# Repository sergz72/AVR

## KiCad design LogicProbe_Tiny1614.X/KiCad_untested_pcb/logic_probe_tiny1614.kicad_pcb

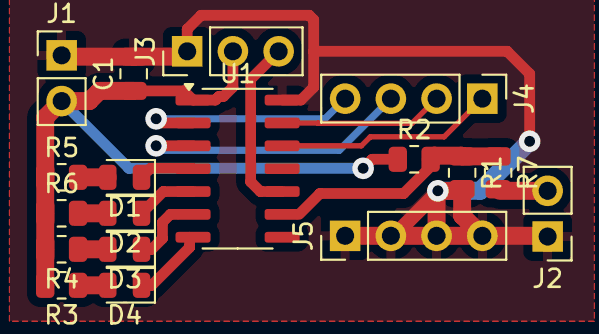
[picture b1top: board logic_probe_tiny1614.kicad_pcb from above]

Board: 2 copper layers, 18 parts (0 on the bottom side), 17 nets.

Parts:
C1: 100n; C_0805_2012Metric
D1, D2, D3, D4: LED; LED_0805_2012Metric
J1: VCC; PinHeader_1x02_P2.54mm_Vertical
J2: IN; PinHeader_1x02_P2.54mm_Vertical
J3: DEBUG; PinHeader_1x03_P2.54mm_Vertical
J4, J5: SW; PinHeader_1x04_P2.54mm_Vertical
R1: 20k; R_0805_2012Metric
R2: 68k; R_0805_2012Metric
R3, R4, R5, R6: 1k; R_0805_2012Metric
R7: 300; R_0805_2012Metric
U1: ATtiny1614-SS; SOIC-14_3.9x8.7mm_P1.27mm

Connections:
GND: C1.2, J1.1, J2.1, J3.1, J5.1, J5.2, J5.3, J5.4, R1.2, U1.14 (GND)
unnamed: D1.2 (A), R5.2
unnamed: D1.1 (K), U1.4 (PA6)
unnamed: D2.2 (A), R6.2
unnamed: D2.1 (K), U1.5 (PA7)
unnamed: D3.2 (A), R4.1
unnamed: D3.1 (K), U1.6 (PB3)
unnamed: D4.2 (A), R3.1
unnamed: D4.1 (K), U1.7 (PB2)
unnamed: C1.1, J1.2, J3.2, R2.1, R3.2, R4.2, R5.1, R6.1, U1.1 (VCC)
unnamed: J2.2, R7.2
unnamed: J3.3, U1.10 (~RESET/PA0)
unnamed: J4.1, U1.12 (PA2)
unnamed: J4.2, U1.13 (PA3)
unnamed: J4.3, U1.3 (PA5)
unnamed: J4.4, U1.2 (PA4)
unnamed: R1.1, R2.2, R7.1, U1.9 (PB0)

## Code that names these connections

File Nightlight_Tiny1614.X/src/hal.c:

#include "board.h"
#include <avr/io.h>
#include <avr/sleep.h>
#include <avr/interrupt.h>
#include <avr/cpufunc.h>
#include <avr/wdt.h>
#include "usart_handler.h"
#include <stdio.h>
#include <rtc_pcf8563.h>
#include <i2c_tiny1614.h>

FUSES = {
  .WDTCFG = 0x07, // WDTCFG {PERIOD=0.5s, WINDOW=OFF}
  .BODCFG = 0x55, // BODCFG {SLEEP=ENABLED, ACTIVE=ENABLED, SAMPFREQ=125HZ, LVL=BODLEVEL2} 2.6v
  .OSCCFG = 0x01, // OSCCFG {FREQSEL=16MHZ, OSCLOCK=CLEAR}
  .TCD0CFG = 0x00, // TCD0CFG {CMPA=CLEAR, CMPB=CLEAR, CMPC=CLEAR, CMPD=CLEAR, CMPAEN=CLEAR, CMPBEN=CLEAR, CMPCEN=CLEAR, CMPDEN=CLEAR}
  .SYSCFG0 = 0xF6, // SYSCFG0 {EESAVE=CLEAR, RSTPINCFG=UPDI, CRCSRC=NOCRC}
  .SYSCFG1 = 0x07, // SYSCFG1 {SUT=64MS}
  .APPEND = 0x00, // APPEND {APPEND=User range:  0x0 - 0xFF}
  .BOOTEND = 0x00, // BOOTEND {BOOTEND=User range:  0x0 - 0xFF}
};

LOCKBITS = 0xC5; // {LB=NOLOCK}

volatile unsigned char timer_interrupt, rtc_interrupt;

#ifdef USART_ENABLED
int usart_fputchar(char c, FILE *stream);
FILE usart_stdout = FDEV_SETUP_STREAM(usart_fputchar, NULL, _FDEV_SETUP_WRITE);
#endif

// RTC counter interrupt
ISR (RTC_PIT_vect)
{
  wdt_reset();
  timer_interrupt = 1;
  RTC.PITINTFLAGS = 1; // clear interrupt flag
}

ISR (INT_PORT_vect)
{
  if (INT_PORT.INTFLAGS & (1 << INT_PIN))
    rtc_interrupt = 1;
  INT_PORT.INTFLAGS = 0xFF;
}

#ifdef USART_ENABLED
ISR (USART0_RXC_vect)
{
  if (USART0.STATUS & 0x80)
  {
    unsigned char c = USART0.RXDATAL;
    usart_interrupt_handler(c);
  }
}
#endif

/*
 * PB0(9)  SCL
 * PB1(8)  SDA
 * PB2(7)  TX
 * PB3(6)  RX
 * PA0(10) UPDI
 * PA1(11) INT
 * PA2(12) LED_TIMER
 * PA3(13) LED_BATTERY
 * PA4(2)  TCD WOA
 * PA5(3)
 * PA6(4)  AC1 AINP1
 * PA7(5)
 */

static void
InitPorts (void)
{
  LED_TIMER_PORT.DIRSET = 1 << LED_TIMER_PIN;
  LED_BATTERY_PORT.DIRSET = 1 << LED_BATTERY_PIN;
  INT_PORT.INT_PINCTRL = 0b00001011; // pullup enable, falling edge interrupt
}

static void
InitRTC (void)
{
  RTC.PITCTRLA   = 0b01011001; // enabled, interrupt each 4096 cycles
  RTC.PITINTCTRL = 1; // periodic interrupt is enabled
}

static void InitVREF(void)
{
  VREF.CTRLA = 0b01000000; // ADC0 reference = 1.5v, DAC0 reference = 0.55v
  VREF.CTRLC = 0b00000000; // ADC1 reference = 0.55v, DAC1 reference = 0.55v
  VREF.CTRLB = 0b00001010; // Enable references for ADC0, DAC1
}

static void InitDAC1(void)
{
  DAC1.DATA  = DAC1_VALUE;
  DAC1.CTRLA = 0x01; // DAC enable
}

static void InitComparator1(void)
{
  PORTA.PIN6CTRL = 4; // digital intput buffer disable
  
  AC1.MUXCTRLA = 0b00001011; // invert output, positive input - AINP1, negative input - DAC
  AC1.CTRLA    = 0b00000001; // Comparator enable, output disable

  // 2. Route AC0 output to Event System Channel 0
  EVSYS.ASYNCCH0   = EVSYS_ASYNCCH0_AC1_OUT_gc; // AC1_OUT
  EVSYS.ASYNCUSER6 = 3; // ASYNCCH0 -> Timer Counter D 0 Event 0
}

static void
InitADC0(void)
{
  ADC0.MUXPOS   = 0x1D; // internal reference
  ADC0.CTRLB    = 0b00000000; // No accumulation
  ADC0.CTRLC    = 0b01010011; // Prescaler: 16, REFSEL = VDD, Reduced size of sampling capacitance. Recommended for higher reference voltages.
  ADC0.SAMPCTRL = 0; // sampling time - two adc cycles
  ADC0.CTRLA    = 0b00000001; // ADC enabled
}

static void
InitPWM(void)
{
  TCD0.CTRLB   = 0; // WGMODE = OneRamp
  TCD0.CTRLC   = 0;
  TCD0.CTRLD   = 0;
  TCD0.CTRLE   = 0;
  TCD0.CMPASET = 0;
  TCD0.CMPACLR = PWM_DUTY;
  TCD0.CMPBSET = 0;
  TCD0.CMPBCLR = PWM_CMP_CALC(PWM_FREQUENCY); // period
  TCD0.INPUTCTRLA = 6; // WAIT
  TCD0.EVCTRLA = 0b10010101; // Async event, rising edge, fault event, enabled
  
  PWM_PORT.DIRSET = 1 << PWM_PIN;
}

#ifdef USART_ENABLED
static void
InitUsart (void)
{
  stdout = &usart_stdout;
  
  // read signed error
  signed char sigrow_val = SIGROW.OSC16ERR3V;
  // ideal BAUD register value
  signed long baud_reg_val = CLK_PER * 4L / USART_BAUD; 
  baud_reg_val *= 1024 + sigrow_val; // sum resolution + error
  baud_reg_val /= 1024; // divide by resolution  
  
  USART0.BAUD  = (unsigned short)baud_reg_val;
  USART0.CTRLA = 0b10000000; // Receive complete interrupt enable
  USART0.CTRLB = 0b11000000; // Receiver and transmitter enabled
  // CMODE Asynchronous Mode; UCPHA enabled; UDORD disabled; CHSIZE Character size: 8 bit; PMODE No Parity; SBMODE 1 stop bit; 
  USART0.CTRLC = 0x3;
  USART0.DBGCTRL = 1;
  
  USART_PORT.OUTSET = 1 << USART_TX_PIN;
  USART_PORT.DIRSET = 1 << USART_TX_PIN;
  USART_PORT.USART_RXPINCTRL = 8; // pullup enable
}

void usart_putchar(char c)
{
  while (!(USART0.STATUS & USART_DREIF_bm))
    ;
  USART0.TXDATAL = c;
}

int usart_fputchar(char c, FILE *stream)
{
  if (c == '\n')
    usart_putchar('\r');
  usart_putchar(c);
  return 0;
}
#endif

void
SystemInit (void)
{
  _PROTECTED_WRITE(CLKCTRL.MCLKCTRLB, 7); //prescaler enabled, division = 16
  InitPorts ();
  InitRTC ();
  InitI2C ();
  InitVREF();
  InitDAC1();
  InitComparator1();
  InitADC0();
  InitPWM();
#ifdef USART_ENABLED
  InitUsart();
#endif

  sleep_enable ();
  set_sleep_mode (SLEEP_MODE_IDLE);
}

unsigned short get_vbat(void)
{
  ADC0.COMMAND = ADC_STCONV_bm;
  while (!(ADC0.INTFLAGS & ADC_RESRDY_bm))
    ;
  return ADC0.RES;
}

void enable_pwm(void)
{
  CPU_CCP = CCP_IOREG_gc;    
  TCD0.FAULTCTRL = TCD_CMPAEN_bm; // Enable Compare A pin/channel for PWM
  TCD0.CTRLA = 1; // enabled, clock = 16 MHz
}

void disable_pwm(void)
{
  CPU_CCP = CCP_IOREG_gc;    
  TCD0.FAULTCTRL = 0; // Disable Compare A pin/channel for PWM
  TCD0.CTRLA = 0; // disabled
}

void pwm_set_duty(unsigned short value)
{
  if (!value && TCD0.CTRLA != 0)
    disable_pwm();
  TCD0.CMPACLR = value;
  TCD0.CTRLE   = 1; // SYNCEOC
  if (value && TCD0.CTRLA == 0)
    enable_pwm();
}

void dac_set(unsigned char value)
{
  DAC1.DATA = value;
}

int i2c_pcf8563_write(const unsigned char *data, int data_length)
{
  return TWI_sendMessage (PCF8563_I2C_ADDRESS, data, data_length);
}

int i2c_pcf8563_transfer(const unsigned char *wdata, int wdata_length, unsigned char *rdata, int rdata_length)
{
  return TWI_transfer(PCF8563_I2C_ADDRESS, wdata, wdata_length, rdata, rdata_length);
}

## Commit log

2019-11-28 Code additions
2024-08-04 New project
2024-08-04 Bug fix
2024-08-05 Bug fixes & 3.3v support
2024-12-15 Charger attiny1614 draft
2024-12-15 Emulator for charger
2024-12-16 EEPROM read/write
2025-02-28 Logic probe PCB and schematic
